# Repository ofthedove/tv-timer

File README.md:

# TV Timer
TV Timer for James. I've been wanting to make 3D printed seven segment displays using RGB LEDs to get big, bright digits that don't cost a fortune. (Why are they so small, and big ones so expensive???) Thia had the idea to use them to make a timer that James can use for screen time. (He's been the oven timer but we keep the kitchen closed off from the kids some of the time.)

The star of the show is the 3D printed body, with seven segment digits, custom indicators, and a 3x4 keypad, all 3D printed. The front and back of the case are held together with a band with a single screw at the bottom, inspired by the kidchenaid mixer design, so that the visible part of the case is entirely free of fasteners. I quite like the look of it too. The back has a hole for the USB C port on the Xiao mainboard, and a speaker grill. There's also a couple of weight compartments inside to add weight near the bottom, to improve the feel and make it less likely to slide around everywhere.

Electronics:
- WS2812 style 5mm LEDs on custom PCBs to make digits and indicators
- MX style keyswitches with diodes on custom PCB for the keypad
- Xiao ESP32-C6 on a piece of proto board for the mainboard
- Adafruit audio BFF and 40mm speaker to add audio

Software:
- EspHome for easy integration with Home Assistant, easy OTA updates, and pre-existing support for single wire LEDs and matrix keypads. (Probably I2S too haven't figured that out yet.)
- Will create custom (a) component(s) for turning single-wire led strand into digits and for the actual timer logic

Features: (Planned)
- Clock mode: When timer is not being used, it will show the current time
- Timer mode: Press the timer button and enter a time to start a timer.
  - Timer indicator shows it's in timer mode instead of clock mode
  - May also have different colors per mode
  - Timer can be paused and resumed with timer button
  - Timer can be cancelled with timer button (3-2-1 countdown?)
- Count Up mode: After a timer completes, the display will start counting up the time since the timer ended
  - Maybe after a short delay?
  - Likely with a different color/animation, may blink the timer indicator.
- Home Assistant integration
  - Control timer from Home Assistant (Start/stop/set time etc)
  - Timer complete events for use in automations
  - Use count-up in integrations (Ex: Turn off TV if timer has been going off for 5 min)
  - Control Lock? Remotely lock out keypad from Home Assistant

## Status
Note: I actually have to separate instances in progress currently. One for the TV, and one I'll use for myself (Show and tell? Clock? Take to work? All of the above?)

Task        | Status | Details
----------- | ------ | -------
SSDs        |  100%  | Design a 3D Printable seven segment display for use with 5mm LEDs with good vision
Enclosure   |  100%  | Design an enclosure to hold everything together, including keypad and indicators
PCBs        |  100%  | Design and order custom PCBs to wire-up LEDs and keypad (hand wiring these _sucks_)
Elec. Asm.  |   75%  | Solder up LEDs and keys, and the mainboard, and make wiring harnesses and figure out how everything connects
Weights     |    0%  | Add weight to the case with plaster of paris/concrete/metal scrap or whatever to improve feel and function
3D Printing |   95%  | Actually print all the parts and do the necessary post processing.
Assemble    |   50%  | Assemble everything together
Software    |    0%  | Here be dragons
HASS        |    0%  | Create some fun automations/dashboards to work with the timer!

## Dev Pictures
This picture shows the digits lit up showing the time

I'm pretty proud of the way the case is held together with a band and a single screw to keep the band in place.

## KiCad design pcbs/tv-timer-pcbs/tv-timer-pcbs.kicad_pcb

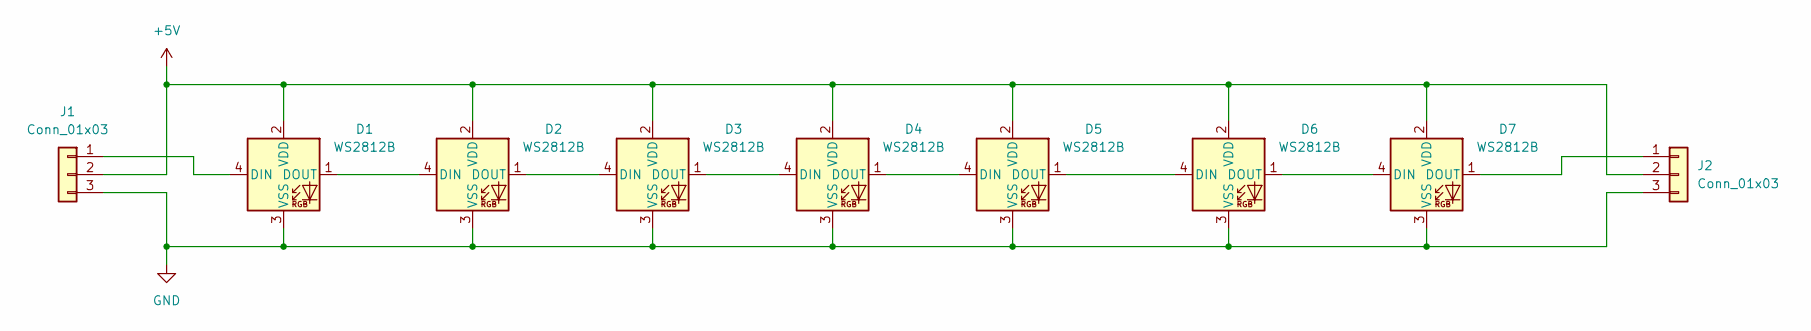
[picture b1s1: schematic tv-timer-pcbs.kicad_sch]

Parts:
D1, D2, D3, D4, D5, D6, D7: WS2812B; LED_D5.0mm-4_RGB_Wide_Pins
J1, J2: Conn_01x03; JST_XH_B3B-XH-AM_1x03_P2.50mm_Vertical

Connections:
+5V: D1.2 (VDD), D2.2 (VDD), D3.2 (VDD), D4.2 (VDD), D5.2 (VDD), D6.2 (VDD), D7.2 (VDD), J1.2, J2.2
GND: D1.3 (VSS), D2.3 (VSS), D3.3 (VSS), D4.3 (VSS), D5.3 (VSS), D6.3 (VSS), D7.3 (VSS), J1.3, J2.3
unnamed: D1.4 (DIN), J1.1
unnamed: D1.1 (DOUT), D2.4 (DIN)
unnamed: D2.1 (DOUT), D3.4 (DIN)
unnamed: D3.1 (DOUT), D4.4 (DIN)
unnamed: D4.1 (DOUT), D5.4 (DIN)
unnamed: D5.1 (DOUT), D6.4 (DIN)
unnamed: D6.1 (DOUT), D7.4 (DIN)
unnamed: D7.1 (DOUT), J2.1

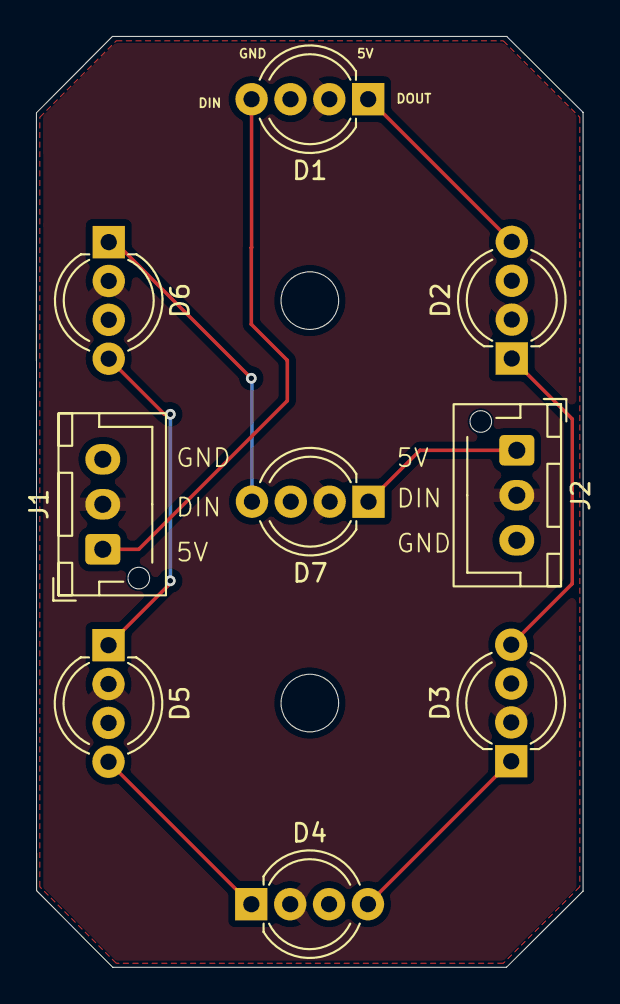
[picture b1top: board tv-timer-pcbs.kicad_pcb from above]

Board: 2 copper layers, 30.4 x 51.7 mm, 9 parts (0 on the bottom side), 10 nets.

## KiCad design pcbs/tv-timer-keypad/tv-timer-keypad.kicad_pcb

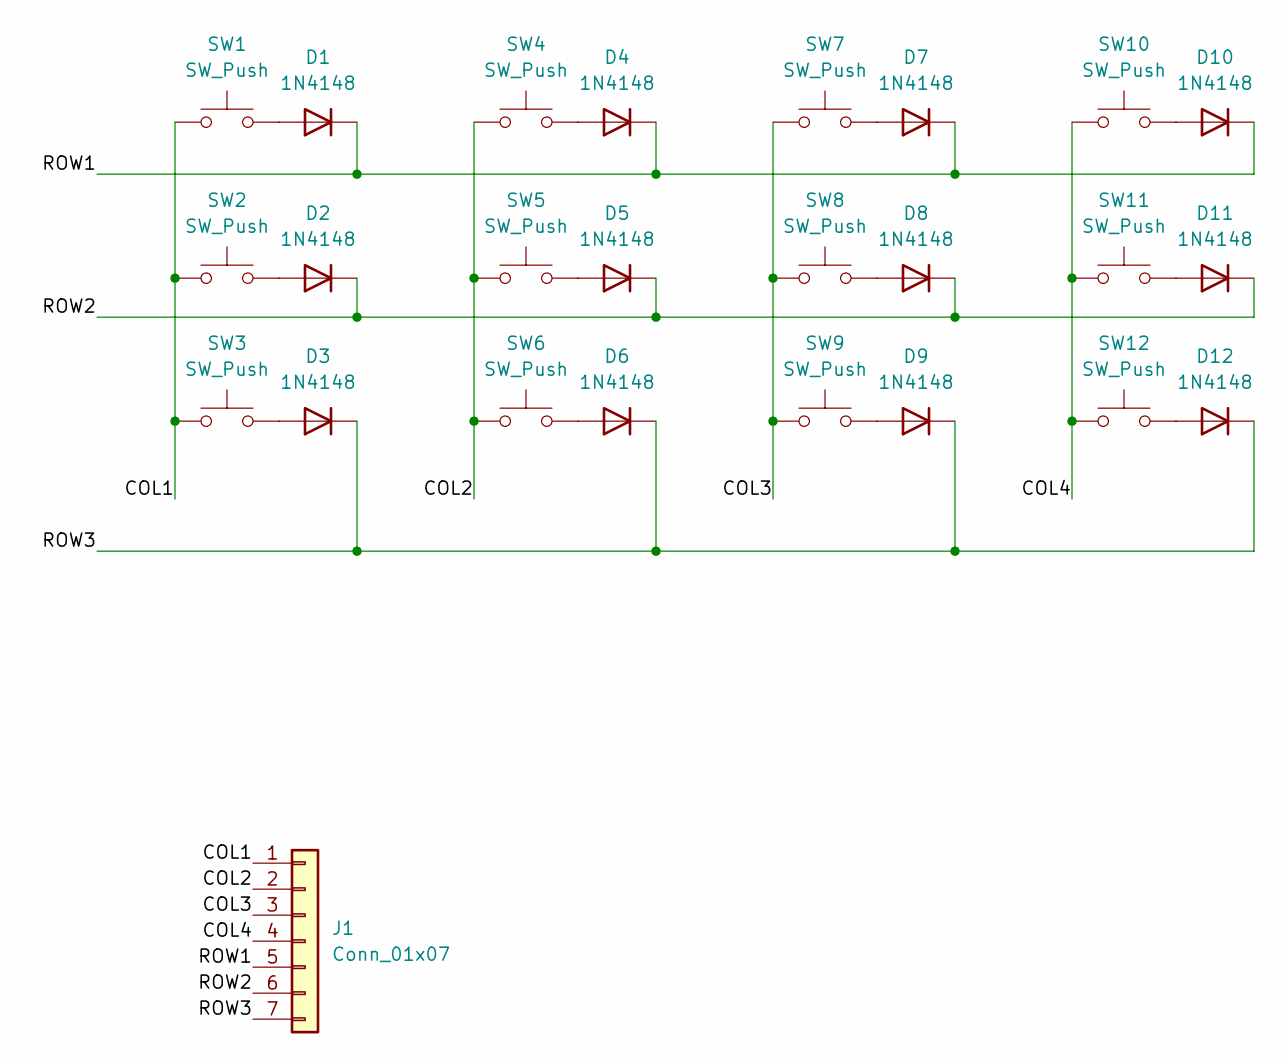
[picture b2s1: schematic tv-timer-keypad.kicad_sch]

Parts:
D1, D2, D3, D4, D5, D6, D7, D8, D9, D10, D11, D12: 1N4148; D_DO-35_SOD27_P7.62mm_Horizontal
J1: Conn_01x07; JST_XH_B7B-XH-AM_1x07_P2.50mm_Vertical
SW1, SW2, SW3, SW4, SW5, SW6, SW7, SW8, SW9, SW10, SW11, SW12: SW_Push; SW_Hybrid_Cherry_MX_Alps

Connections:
/COL1: J1.1, SW1.1, SW2.1, SW3.1
/COL2: J1.2, SW4.1, SW5.1, SW6.1
/COL3: J1.3, SW7.1, SW8.1, SW9.1
/COL4: J1.4, SW10.1, SW11.1, SW12.1
/ROW1: D1.1 (K), D4.1 (K), D7.1 (K), D10.1 (K), J1.5
/ROW2: D2.1 (K), D5.1 (K), D8.1 (K), D11.1 (K), J1.6
/ROW3: D3.1 (K), D6.1 (K), D9.1 (K), D12.1 (K), J1.7
unnamed: D1.2 (A), SW1.2
unnamed: D2.2 (A), SW2.2
unnamed: D3.2 (A), SW3.2
unnamed: D4.2 (A), SW4.2
unnamed: D5.2 (A), SW5.2
unnamed: D6.2 (A), SW6.2
unnamed: D7.2 (A), SW7.2
unnamed: D8.2 (A), SW8.2
unnamed: D9.2 (A), SW9.2
unnamed: D10.2 (A), SW10.2
unnamed: D11.2 (A), SW11.2
unnamed: D12.2 (A), SW12.2

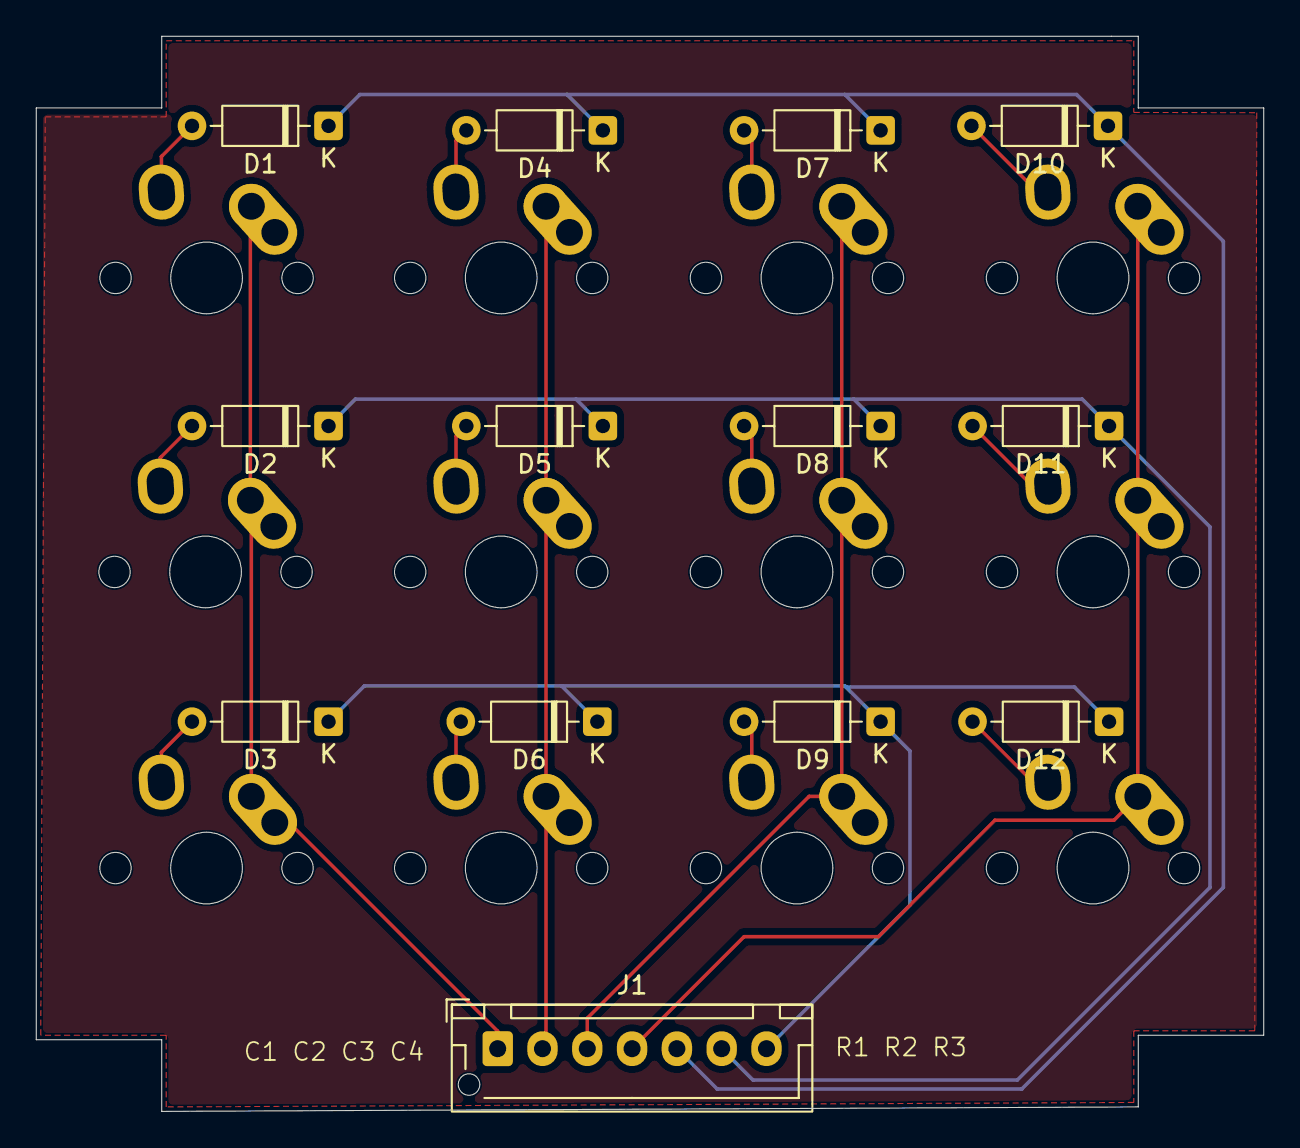
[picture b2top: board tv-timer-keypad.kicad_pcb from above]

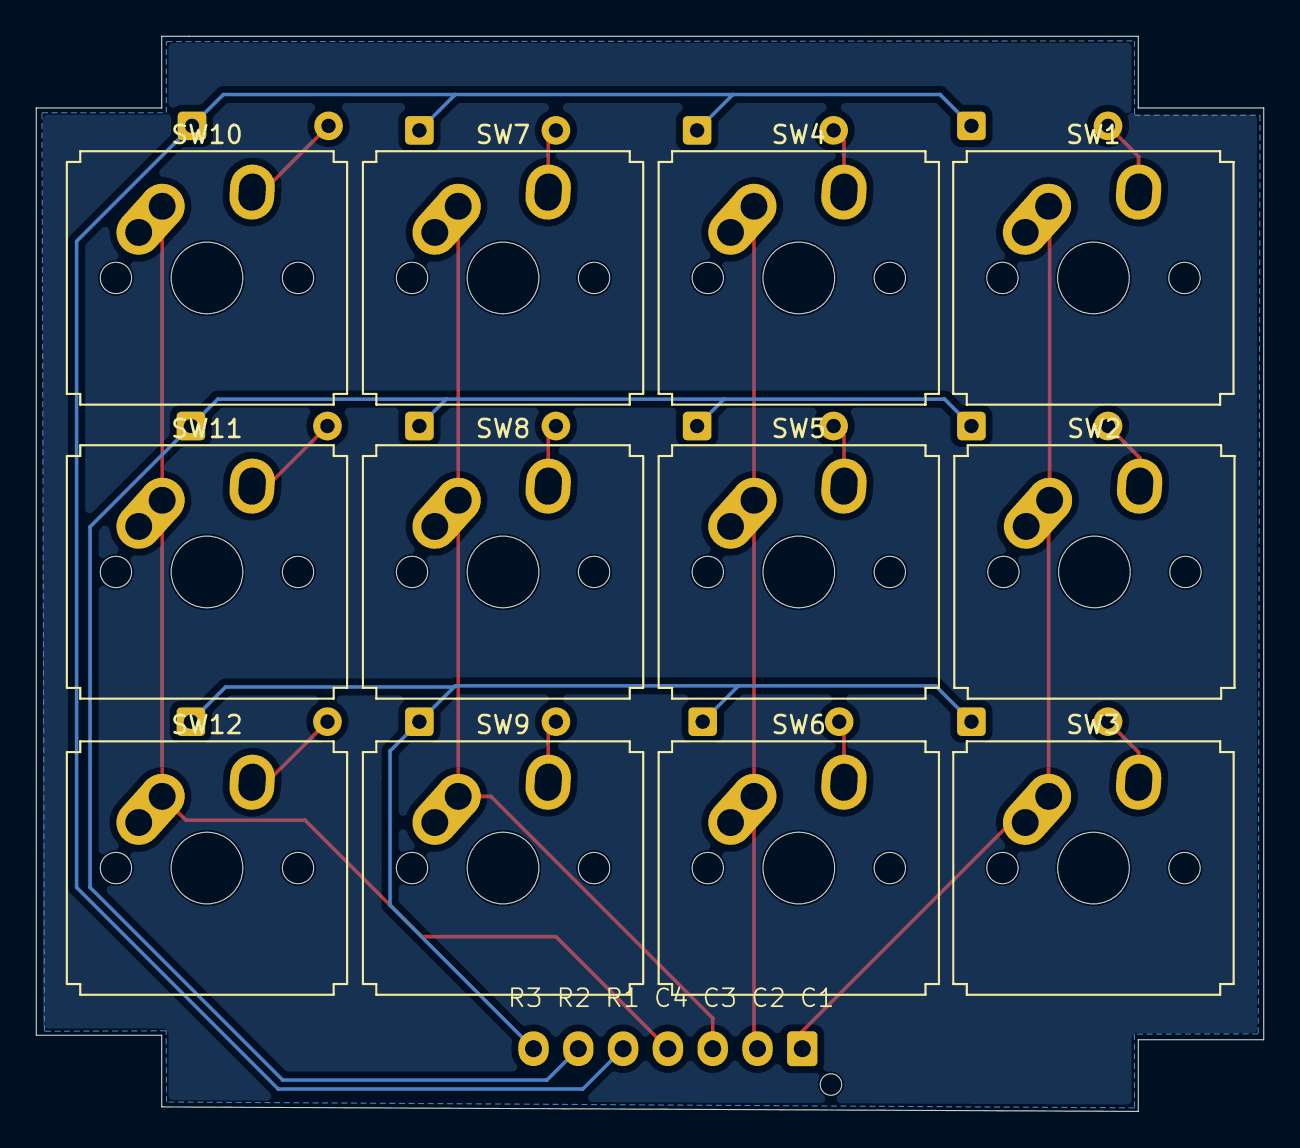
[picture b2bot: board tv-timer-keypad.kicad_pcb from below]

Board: 2 copper layers, 68.5 x 60.0 mm, 25 parts (12 on the bottom side), 19 nets.
